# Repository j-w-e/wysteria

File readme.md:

# JWE's custom split keyboard, the Wysteria

This is my custom split 36-key keyboard, with an encoder knob on each hand, and a pinky cluster to avoid stretching my pinky – I find lateral movement easier.

The pcbs, and the source ergogen file used to generate v0.3, can be found in the pcbs folder.

It has working firmware for both QMK and ZMK. Source files are in the repo, but I have not put this into the main repos for either QMK or ZMK. My own build process symlinks these as appropriate.

## NOTES
v0.3 has been printed and tested, and is my current daily driver. However, please note that to build it, the diodes on the thumb cluster need to be handwired to the rows. The traces on the PCB itself are incorrect. This has been fixed in the ergogen config file, ready for if and when I print it again, but this has not had all the traces set up in KiCad, and has not been printed or tested.

* Will (should) work with both QMK (with an oled and trrs) and ZMK (with nice!nano and nice!view)
* If using a display, make sure to solder the jumpers _on the opposite side_ of the board to where the dislay is mounted. This is different to the MCU jumpers, which should be soldered on the same side as the MCU (if mounting face-up)
* The ergogen config places an extra diode below the middle finger, bottom row. I manually replace this in KiCad with the Wysteria graphic. (I haven't worked out how to make the graphic into an ergogen-compatible footprint. I'm happy with the manual step for now.)

## Parts used
* [Liatris](https://splitkb.com/collections/keyboard-parts/products/liatris) or [nice!nano](https://splitkb.com/collections/keyboard-parts/products/nice-nano)
* [OLED displays](https://www.aliexpress.com/item/32850288143.html?spm=a2g0o.order_list.order_list_main.40.77df1802Ut4SVX) or [nice!view](https://splitkb.com/collections/keyboard-parts/products/nice-view)
* [Sockets](https://www.aliexpress.com/item/32980406694.html?spm=a2g0o.order_list.order_list_main.5.21ef1802pi0AaX)
* [Batteries](https://www.aliexpress.com/item/4000377326948.html?spm=a2g0o.order_list.order_list_main.29.77df1802Ut4SVX) for wireless builds
* [Reset switches](https://www.aliexpress.com/item/32912263133.html?spm=a2g0o.order_list.order_list_main.15.21ef1802pi0AaX)
* [Hotswap sockets](https://www.aliexpress.com/item/1005003873653184.html?spm=a2g0o.order_list.order_list_main.21.21ef1802pi0AaX)
* [Power switches](https://www.aliexpress.com/item/1005003308186629.html?spm=a2g0o.order_list.order_list_main.26.21ef1802pi0AaX) for wireless builds
* [Socket pins](https://www.aliexpress.com/item/4000062247368.html?spm=a2g0o.order_list.order_list_main.31.21ef1802pi0AaX)
* [Diodes](https://www.aliexpress.com/item/32660088529.html?spm=a2g0o.order_list.order_list_main.5.21ef1802a9afJe)
* [EC11](https://www.aliexpress.com/item/1005003824684681.html?spm=a2g0o.cart.0.0.5d5838daGifwXE&mp=1)
* [EC11 knob](https://github.com/GEIGEIGEIST/KLOR/tree/main/knob) from GEIST
* [M2 screws](url)
* Switches and keycaps (all 1u). My current set-up has [Boba U4](https://splitkb.com/collections/switches-and-keycaps/products/gazzew-boba-u4-silent-tactile-switch?_pos=1&_fid=bebc80122&_ss=c) in the office, [Boba U4Tx](https://splitkb.com/collections/switches-and-keycaps/products/gazzew-boba-u4tx-thocky-tactile-switch?_pos=7&_fid=bebc80122&_ss=c) at home, and [DES](https://github.com/sporkus/PseudoMakeMeKeyCapProfiles/tree/master/stl/MX) printed by JLCPCB

### Tenting set-up

* [Z-fold tripod](https://www.aliexpress.com/item/1005006313678530.html)
* [Magsafe tripod adapter](https://www.aliexpress.com/item/1005006074567830.html)
* [Folding laptop stands](https://www.temu.com/goods.html?_bg_fs=1&goods_id=601099538883858&_x_sessn_id=7odffn4414)

## To do

If I ever decide to build a new one, want to:

* ~~Fix the problem of the thumb cluster not being in the matrix~~
* Move the thumb keys slightly further down (ie closer to the wrist). My thumbs naturally rest so that only the very tip is on the key.
* Rotate the lateral pinky key by 90 degrees, so that the keycap can be rotated as well.
* Move the lateral pinky key down 2mm.
* Move the reset switch to a more sensible location, though where that is I don't currently know.
* If I am feeling very ambitious, think about making a steel plate as a base, so it attaches cleanly to the magsafe tripod adapter. But I would need to work out how to properly countersink the screws, and rethink where the screws are.

## References

Made based on
* [ergogen](https://github.com/ergogen/ergogen)
* [FlatFootFox's ergogen intro](https://flatfootfox.com/ergogen-introduction/)
* [TSteffek's guide to ergogen v4 compared to v3](https://github.com/tsteffek/Ergogen-V4-Migration-Guide)
* Kvietcong's fork of [ergogen](https://github.com/kvietcong/ergogen) (for the footprints)
* Ceoloide's [corney-island](https://github.com/ceoloide/corney-island)
* Narkoleptika's [josukey](https://github.com/Narkoleptika/josukey)

### Guides for other parts

### Keyboards used as reference
* [Rae-dux](https://github.com/andrewjrae/rae-dux) (especially the build guide from [tzcl](https://www.tzcl.me/blog/rae-dux) for parts references)
* [Claw](https://gitlab.com/Audijo/keyboard) (for ergogen)
* [Piano](https://github.com/benvallack/ergogen/blob/master/input/config-piano.yaml)
* [PicaChoc36](https://github.com/zzeneg/picachoc36) (eg for parts references)
* [Swoop](https://github.com/jimmerricks/swoop) (eg for parts references)
* [Klor](https://github.com/GEIGEIGEIST/KLOR/blob/main/docs/buildguide_acrylic_ble.md)
* [Sofle](https://josefadamcik.github.io/SofleKeyboard/sourcing_parts.html)

### Other references:
* Sadek Baroudi's [guide to making cases](https://github.com/sadekbaroudi/keyboard-guides/blob/master/cases/README.md)
* Ben Vallack's [video on using ergogen](https://www.youtube.com/watch?v=M_VuXVErD6E) (nb: outdated as it is based on ergogen v3)
* [Batteries](https://github.com/joric/nrfmicro/wiki/Batteries#301230)
* The Absolem [build guide](https://zealot.hu/absolem/#build)

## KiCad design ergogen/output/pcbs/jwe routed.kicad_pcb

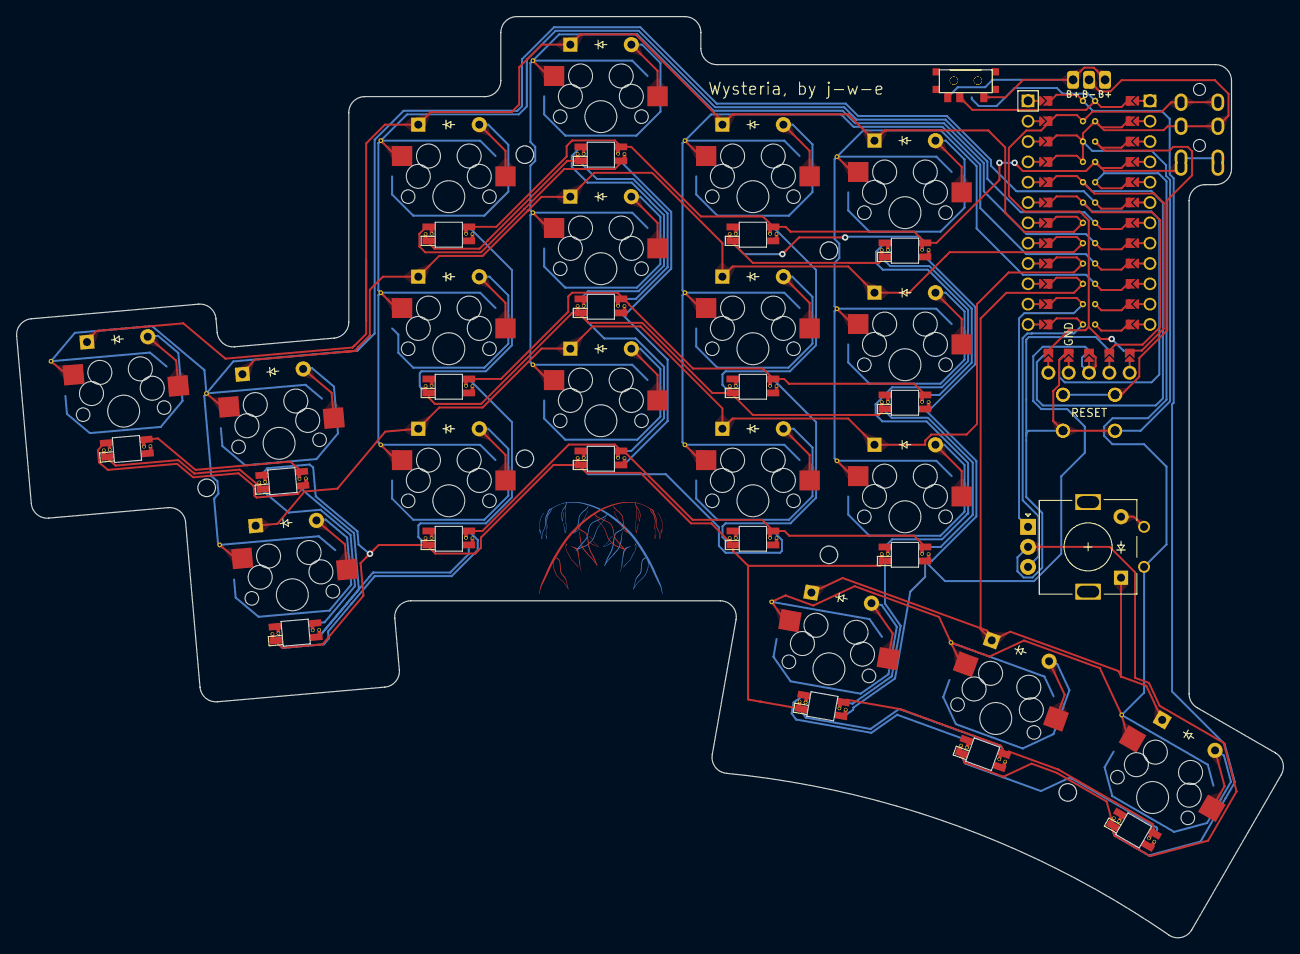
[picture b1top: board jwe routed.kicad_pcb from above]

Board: 2 copper layers, 158.3 x 115.1 mm, 66 parts (1 on the bottom side), 57 nets.

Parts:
B1, B2: SW_TACT_ALPS_SKQGABE010
D1, D2, D3, D4, D5, D6, D7, D8, D9, D10, D11, D12, D13, D14, D15, D16, D17, D18, D19: ComboDiode
D20, D20#2: Wysteria
JST1: bat
L9, L9#2, L9#3, L9#4, L9#5, L9#6, L9#7, L9#8, L9#9, L9#10, L9#11, L9#12, L9#13, L9#14, L9#15, L9#16, L9#17, L9#18: SK6812Mini-e; WS2812B
ROT1: rotary_encoder
S1, S2, S3, S4, S5, S6, S7, S8, S9, S10, S11, S12, S13, S14, S15, S16, S17, S18: MX
SCREEN1: combo_display
T1, T2: SPDT_C128955
TRRS1: TRRS-PJ-320A-dual
_1: ProMicro

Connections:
GND: B1.2, B2.2, JST1.2, L9.3, L9#2.3, L9#3.3, L9#4.3, L9#5.3, L9#6.3, L9#7.3, L9#8.3, L9#9.3, L9#10.3, L9#11.3, L9#12.3, L9#13.3, L9#14.3, L9#15.3, L9#16.3, L9#17.3, L9#18.3, ROT1.C, SCREEN1.1, TRRS1.3, _1.2, _1.21, _1.22
LED_1: L9#6.2, L9#17.4
LED_2: L9.4, L9#17.2
LED_3: L9.2, L9#9.4
LED_4: L9#9.2, L9#11.4
LED_5: L9#7.4, L9#11.2
LED_6: L9#7.2, L9#14.4
LED_7: L9#4.4, L9#14.2
LED_8: L9#4.2, L9#12.4
LED_9: L9#5.4, L9#12.2
LED_10: L9#5.2, L9#15.4
LED_11: L9#8.4, L9#15.2
LED_12: L9#8.2, L9#13.4
LED_13: L9#13.2, L9#18.4
LED_14: L9#16.4, L9#18.2
LED_15: L9#3.4, L9#16.2
LED_16: L9#2.4, L9#3.2
LED_17: L9#2.2, L9#10.4
RAW: T1.2, T2.2, _1.1
RST: B1.1, B2.1, _1.3
VCC: L9.1, L9#2.1, L9#3.1, L9#4.1, L9#5.1, L9#6.1, L9#7.1, L9#8.1, L9#9.1, L9#10.1, L9#11.1, L9#12.1, L9#13.1, L9#14.1, L9#15.1, L9#16.1, L9#17.1, L9#18.1, SCREEN1.2, TRRS1.1, TRRS1.2, _1.4
bat: JST1.1, T1.1, T2.1
c_index: S10.2, S11.2, S12.2, _1.9
c_inner: S13.2, S14.2, S15.2, _1.10
c_middle: S7.2, S8.2, S9.2, _1.8
c_pinkie: S1.2, S2.2, S3.2, _1.6
c_ring: S4.2, S5.2, S6.2, _1.7
c_thumb: ROT1.2, S16.2, S17.2, S18.2, _1.5
central_home: D17.2, S17.1
data: SCREEN1.5, TRRS1.4, _1.23
index_bottom: D10.2, S10.1
index_home: D11.2, S11.1
index_top: D12.2, S12.1
inner_bottom: D13.2, S13.1
inner_home: D14.2, S14.1
inner_top: D15.2, S15.1
led: L9#6.4, _1.24
middle_bottom: D7.2, S7.1
middle_home: D8.2, S8.1
middle_top: D9.2, S9.1
mosi: SCREEN1.4, SCREEN1.5, _1.20
pinkie_bottom: D1.2, S1.1
pinkie_home: D2.2, S2.1
pinkie_top: D3.2, S3.1
r_bottom: D1.1, D4.1, D7.1, D10.1, D13.1, _1.16
r_home: D2.1, D5.1, D8.1, D11.1, D14.1, _1.17
r_thumb: D16.1, D17.1, D18.1, D19.1, _1.15
r_top: D3.1, D6.1, D9.1, D12.1, D15.1, _1.18
ring_bottom: D4.2, S4.1
ring_home: D5.2, S5.1
ring_top: D6.2, S6.1
rot_anticlock: ROT1.B, _1.13
rot_clock: ROT1.A, _1.14
rotary_key: D19.2, ROT1.1
sck: SCREEN1.3, _1.19
stretchie_home: D18.2, S18.1
tuckie_home: D16.2, S16.1

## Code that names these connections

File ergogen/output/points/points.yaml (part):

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        autobind: 10
        skip: false
        asym: both
        colrow: pinkie_bottom
        name: main_pinkie_bottom
        bind:
            - 1
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            - 1
        tags:
            alphas: true
        col_net: c_pinkie
        row_net: r_bottom
        key: &ref_0
            led_prev: LED_15
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            columns:
                pinkie: &ref_1
                    key:
                        col_net: c_pinkie
                    rows:
                        top:
                            adjust:
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        autobind: 10
        skip: false
        asym: both
        colrow: pinkie_home
        name: main_pinkie_home
        bind:
            - 1
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            - 1
        tags:
            alphas: true
        col_net: c_pinkie
        row_net: r_home
        key: *ref_2
        zone: *ref_3
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        autobind: 10
        skip: false
        asym: both
        colrow: pinkie_top
        name: main_pinkie_top
        bind:
            - 1
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            - 1
        tags:
            alphas: true
        col_net: c_pinkie
        row_net: r_top
        key: *ref_5
        zone: *ref_3
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
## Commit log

2024-03-10 First sharing of wysteria
2024-04-19 updating readme.md
2024-04-19 updating readme
2024-04-19 adding zmk and qmk default keymaps
